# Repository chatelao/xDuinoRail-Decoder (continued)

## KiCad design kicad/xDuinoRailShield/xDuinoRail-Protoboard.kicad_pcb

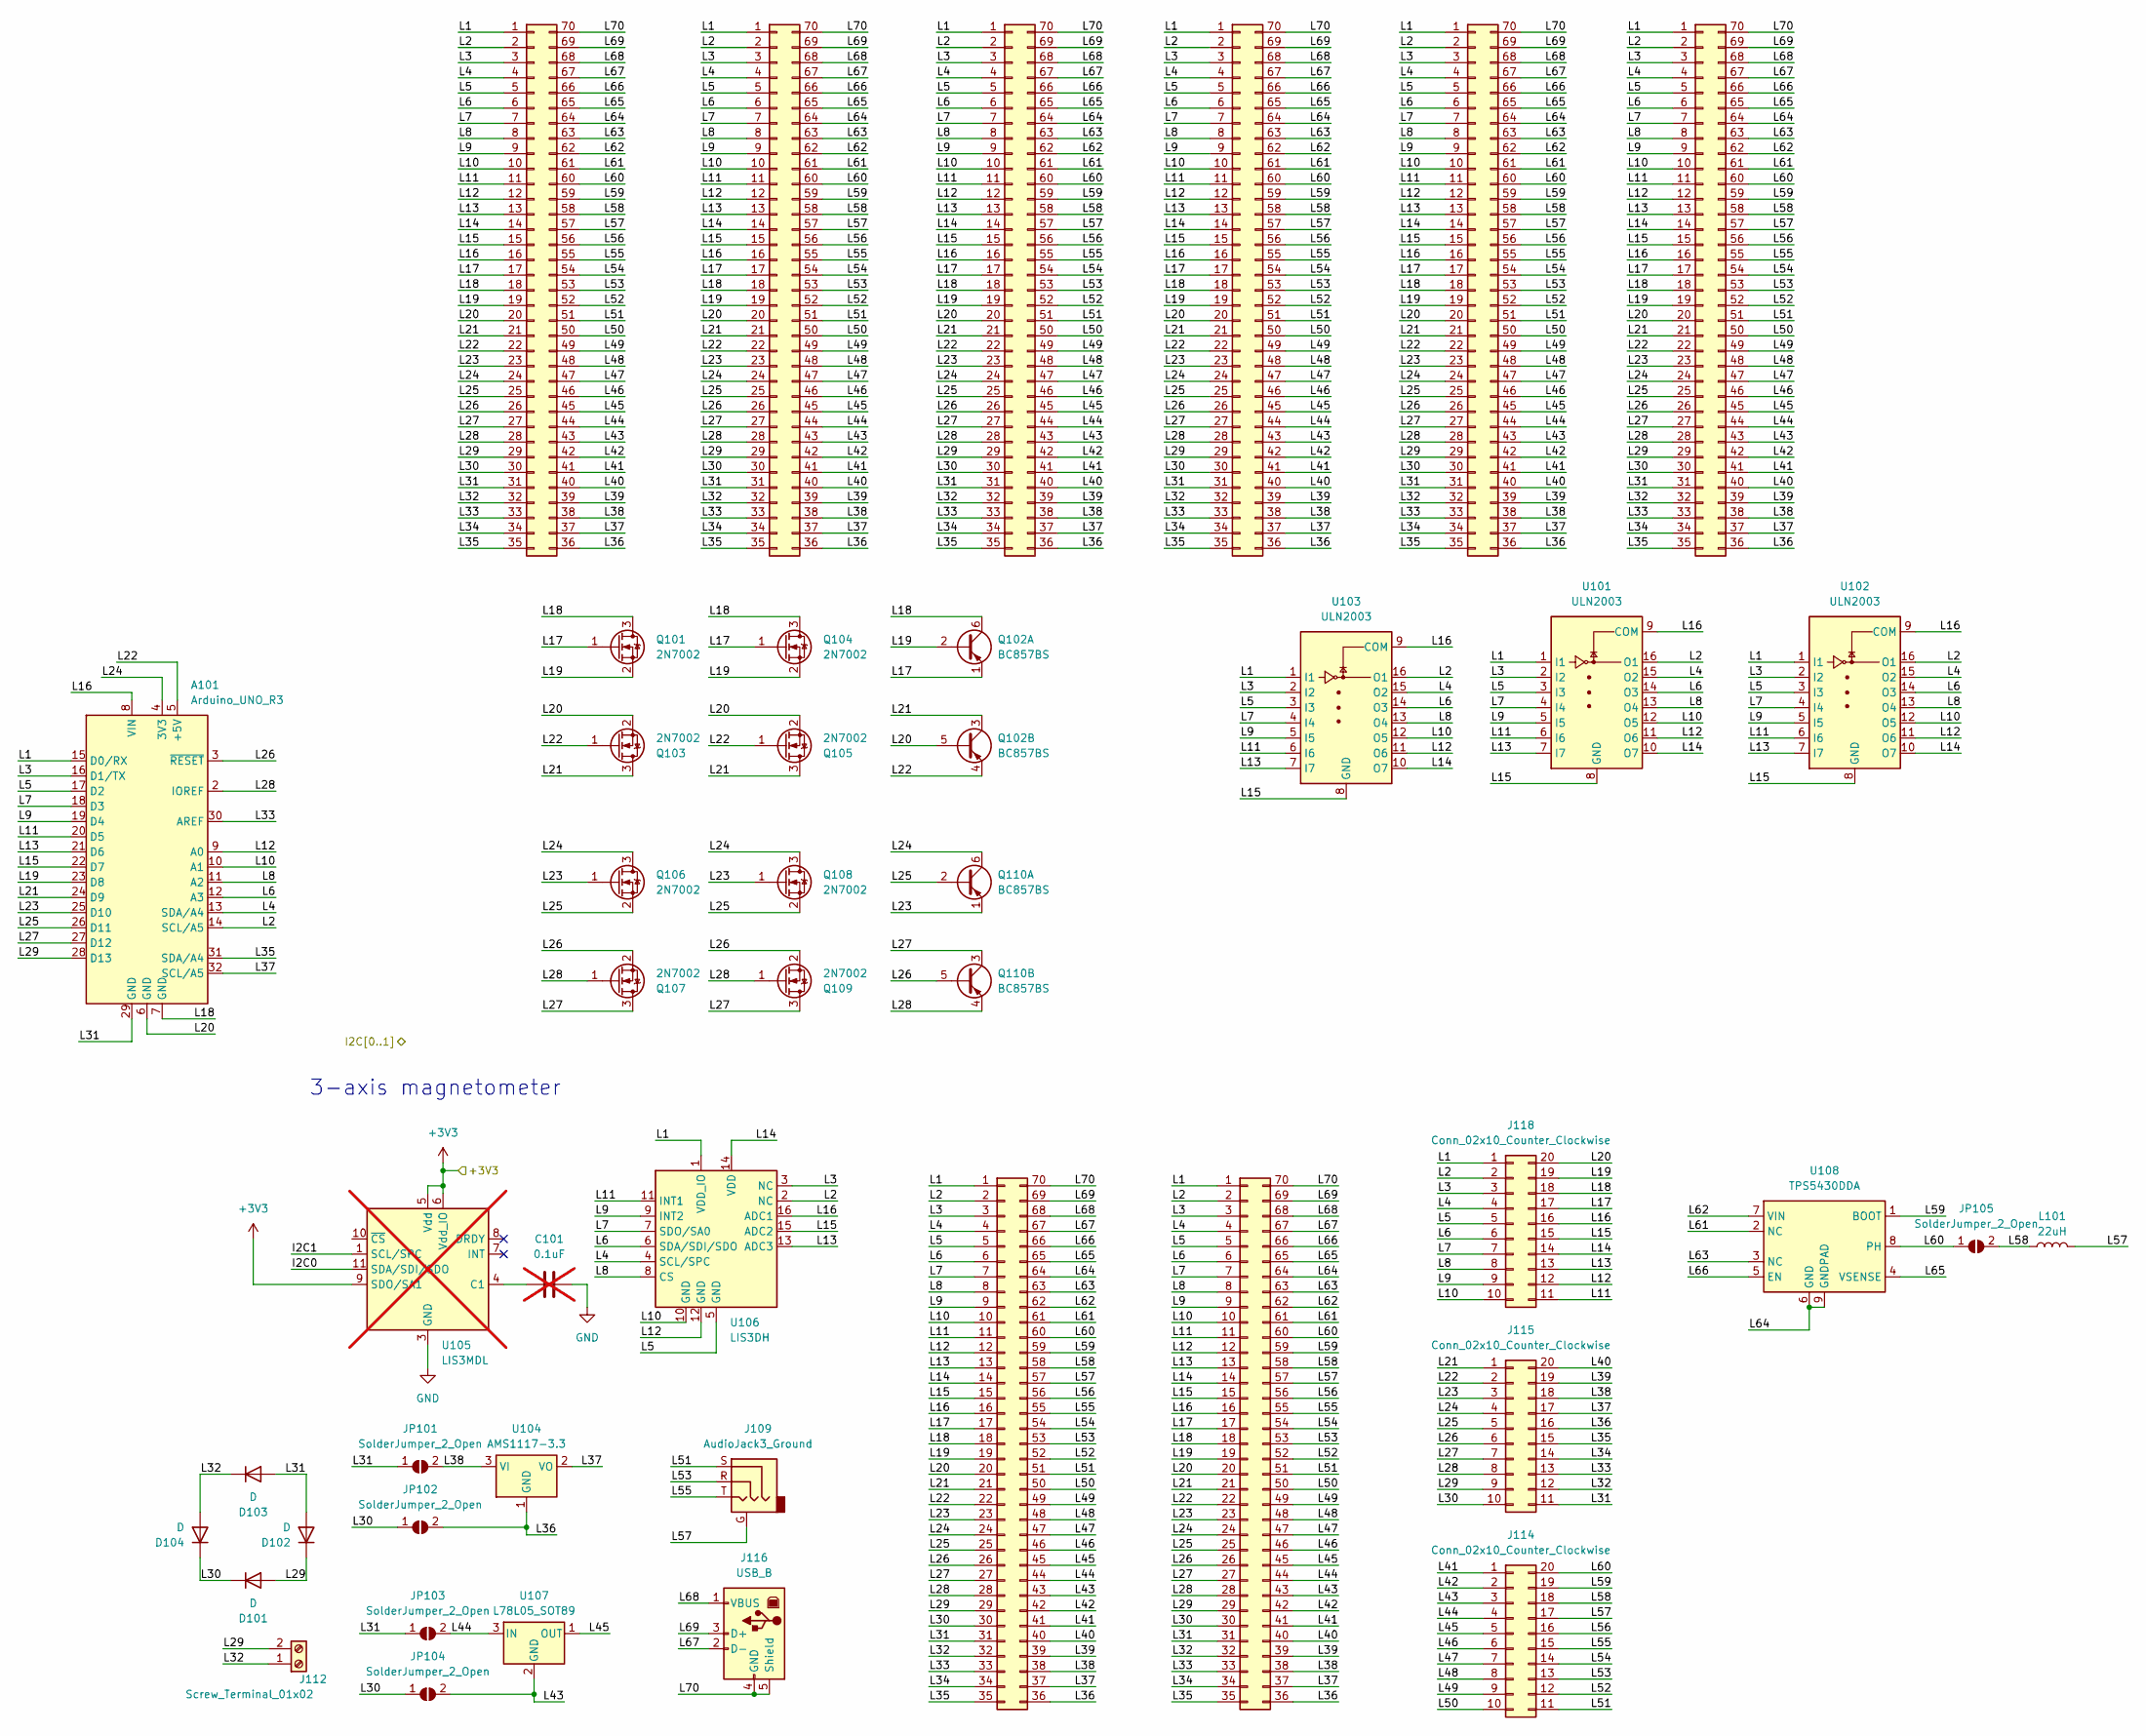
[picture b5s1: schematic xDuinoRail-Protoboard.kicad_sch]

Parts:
A101: Arduino_UNO_R3
C101: 0.1uF; C_0805_2012Metric_Pad1.18x1.45mm_HandSolder; not fitted
D101, D102, D103, D104: D; D_SMA-SMB_Universal_Handsoldering
J101, J102, J103, J104, J105, J106, J110, J111: Conn_02x35_Counter_Clockwise; PinHeader_2x35_P2.54mm_Vertical_Proto
J109: AudioJack3_Ground; Jack_3.5mm_Lumberg_1503_03_Horizontal
J112: Screw_Terminal_01x02; TerminalBlock_bornier-2_P5.08mm
J114: Conn_02x10_Counter_Clockwise; PinHeader_2x10_P1.27mm_Vertical
J115: Conn_02x10_Counter_Clockwise; PinHeader_2x10_P1.00mm_Vertical
J116: USB_B; USB_B_OST_USB-B1HSxx_Horizontal
J118: Conn_02x10_Counter_Clockwise; PinHeader_2x10_P2.00mm_Vertical
JP101, JP102, JP103, JP104, JP105: SolderJumper_2_Open; SolderJumper-2_P1.3mm_Open_TrianglePad1.0x1.5mm
L101: 22uH; L_12x12mm_H8mm; LCSC C693888
Q101, Q103, Q104, Q105, Q106, Q107, Q108, Q109: 2N7002; SOT-23_Handsoldering
Q102, Q110: BC857BS; SOT-363_SC-70-6
U101, U103: ULN2003; SOIC-16_3.9x9.9mm_P1.27mm
U102: ULN2003; SSOP-16_3.9x4.9mm_P0.635mm
U104: AMS1117-3.3; SOT-223-3_TabPin2
U105: LIS3MDL; LGA-12_2x2mm_P0.5mm; LCSC C478483; not fitted
U106: LIS3DH; LGA-16_3x3mm_P0.5mm_LayoutBorder3x5y; LCSC C15134
U107: L78L05_SOT89; SOT-89-3
U108: TPS5430DDA; TI_SO-PowerPAD-8_ThermalVias; LCSC C9864

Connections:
/L1: A101.15 (D0/RX), J101.1, J102.1, J103.1, J104.1, J105.1, J106.1, J110.1, J111.1, J118.1, U101.1 (I1), U102.1 (I1), U103.1 (I1), U106.1 (VDD_IO)
/L2: A101.14 (SCL/A5), J101.2, J102.2, J103.2, J104.2, J105.2, J106.2, J110.2, J111.2, J118.2, U101.16 (O1), U102.16 (O1), U103.16 (O1), U106.2 (NC)
/L3: A101.16 (D1/TX), J101.3, J102.3, J103.3, J104.3, J105.3, J106.3, J110.3, J111.3, J118.3, U101.2 (I2), U102.2 (I2), U103.2 (I2), U106.3 (NC)
/L4: A101.13 (SDA/A4), J101.4, J102.4, J103.4, J104.4, J105.4, J106.4, J110.4, J111.4, J118.4, U101.15 (O2), U102.15 (O2), U103.15 (O2), U106.4 (SCL/SPC)
/L5: A101.17 (D2), J101.5, J102.5, J103.5, J104.5, J105.5, J106.5, J110.5, J111.5, J118.5, U101.3 (I3), U102.3 (I3), U103.3 (I3), U106.5 (GND)
/L6: A101.12 (A3), J101.6, J102.6, J103.6, J104.6, J105.6, J106.6, J110.6, J111.6, J118.6, U101.14 (O3), U102.14 (O3), U103.14 (O3), U106.6 (SDA/SDI/SDO)
/L7: A101.18 (D3), J101.7, J102.7, J103.7, J104.7, J105.7, J106.7, J110.7, J111.7, J118.7, U101.4 (I4), U102.4 (I4), U103.4 (I4), U106.7 (SDO/SA0)
/L8: A101.11 (A2), J101.8, J102.8, J103.8, J104.8, J105.8, J106.8, J110.8, J111.8, J118.8, U101.13 (O4), U102.13 (O4), U103.13 (O4), U106.8 (CS)
/L9: A101.19 (D4), J101.9, J102.9, J103.9, J104.9, J105.9, J106.9, J110.9, J111.9, J118.9, U101.5 (I5), U102.5 (I5), U103.5 (I5), U106.9 (INT2)
/L10: A101.10 (A1), J101.10, J102.10, J103.10, J104.10, J105.10, J106.10, J110.10, J111.10, J118.10, U101.12 (O5), U102.12 (O5), U103.12 (O5), U106.10 (GND)
/L11: A101.20 (D5), J101.11, J102.11, J103.11, J104.11, J105.11, J106.11, J110.11, J111.11, J118.11, U101.6 (I6), U102.6 (I6), U103.6 (I6), U106.11 (INT1)
/L12: A101.9 (A0), J101.12, J102.12, J103.12, J104.12, J105.12, J106.12, J110.12, J111.12, J118.12, U101.11 (O6), U102.11 (O6), U103.11 (O6), U106.12 (GND)
/L13: A101.21 (D6), J101.13, J102.13, J103.13, J104.13, J105.13, J106.13, J110.13, J111.13, J118.13, U101.7 (I7), U102.7 (I7), U103.7 (I7), U106.13 (ADC3)
/L14: J101.14, J102.14, J103.14, J104.14, J105.14, J106.14, J110.14, J111.14, J118.14, U101.10 (O7), U102.10 (O7), U103.10 (O7), U106.14 (VDD)
/L15: A101.22 (D7), J101.15, J102.15, J103.15, J104.15, J105.15, J106.15, J110.15, J111.15, J118.15, U101.8 (GND), U102.8 (GND), U103.8 (GND), U106.15 (ADC2)
/L16: A101.8 (VIN), J101.16, J102.16, J103.16, J104.16, J105.16, J106.16, J110.16, J111.16, J118.16, U101.9 (COM), U102.9 (COM), U103.9 (COM), U106.16 (ADC1)
/L17: J101.17, J102.17, J103.17, J104.17, J105.17, J106.17, J110.17, J111.17, J118.17, Q101.1 (G), Q102.1 (E1), Q104.1 (G)
/L18: A101.7 (GND), J101.18, J102.18, J103.18, J104.18, J105.18, J106.18, J110.18, J111.18, J118.18, Q101.3 (D), Q102.6 (C1), Q104.3 (D)
/L19: A101.23 (D8), J101.19, J102.19, J103.19, J104.19, J105.19, J106.19, J110.19, J111.19, J118.19, Q101.2 (S), Q102.2 (B1), Q104.2 (S)
/L20: A101.6 (GND), J101.20, J102.20, J103.20, J104.20, J105.20, J106.20, J110.20, J111.20, J118.20, Q102.5 (B2), Q103.2 (S), Q105.2 (S)
/L21: A101.24 (D9), J101.21, J102.21, J103.21, J104.21, J105.21, J106.21, J110.21, J111.21, J115.1, Q102.3 (C2), Q103.3 (D), Q105.3 (D)
/L22: A101.5 (+5V), J101.22, J102.22, J103.22, J104.22, J105.22, J106.22, J110.22, J111.22, J115.2, Q102.4 (E2), Q103.1 (G), Q105.1 (G)
/L23: A101.25 (D10), J101.23, J102.23, J103.23, J104.23, J105.23, J106.23, J110.23, J111.23, J115.3, Q106.1 (G), Q108.1 (G), Q110.1 (E1)
/L24: A101.4 (3V3), J101.24, J102.24, J103.24, J104.24, J105.24, J106.24, J110.24, J111.24, J115.4, Q106.3 (D), Q108.3 (D), Q110.6 (C1)
/L25: A101.26 (D11), J101.25, J102.25, J103.25, J104.25, J105.25, J106.25, J110.25, J111.25, J115.5, Q106.2 (S), Q108.2 (S), Q110.2 (B1)
/L26: A101.3 (~RESET), J101.26, J102.26, J103.26, J104.26, J105.26, J106.26, J110.26, J111.26, J115.6, Q107.2 (S), Q109.2 (S), Q110.5 (B2)
/L27: A101.27 (D12), J101.27, J102.27, J103.27, J104.27, J105.27, J106.27, J110.27, J111.27, J115.7, Q107.3 (D), Q109.3 (D), Q110.3 (C2)
/L28: A101.2 (IOREF), J101.28, J102.28, J103.28, J104.28, J105.28, J106.28, J110.28, J111.28, J115.8, Q107.1 (G), Q109.1 (G), Q110.4 (E2)
/L29: A101.28 (D13), D101.2 (A), D102.1 (K), J101.29, J102.29, J103.29, J104.29, J105.29, J106.29, J110.29, J111.29, J112.2, J115.9
/L30: D101.1 (K), D104.1 (K), J101.30, J102.30, J103.30, J104.30, J105.30, J106.30, J110.30, J111.30, J115.10, JP102.1 (A), JP104.1 (A)
/L31: A101.29 (GND), D102.2 (A), D103.2 (A), J101.31, J102.31, J103.31, J104.31, J105.31, J106.31, J110.31, J111.31, J115.11, JP101.1 (A), JP103.1 (A)
/L32: D103.1 (K), D104.2 (A), J101.32, J102.32, J103.32, J104.32, J105.32, J106.32, J110.32, J111.32, J112.1, J115.12
/L33: A101.30 (AREF), J101.33, J102.33, J103.33, J104.33, J105.33, J106.33, J110.33, J111.33, J115.13
/L34: J101.34, J102.34, J103.34, J104.34, J105.34, J106.34, J110.34, J111.34, J115.14
/L35: A101.31 (SDA/A4), J101.35, J102.35, J103.35, J104.35, J105.35, J106.35, J110.35, J111.35, J115.15
/L36: J101.36, J102.36, J103.36, J104.36, J105.36, J106.36, J110.36, J111.36, J115.16, JP102.2 (B), U104.1 (GND)
/L37: A101.32 (SCL/A5), J101.37, J102.37, J103.37, J104.37, J105.37, J106.37, J110.37, J111.37, J115.17, U104.2 (VO)
/L38: J101.38, J102.38, J103.38, J104.38, J105.38, J106.38, J110.38, J111.38, J115.18, JP101.2 (B), U104.3 (VI)
/L39: J101.39, J102.39, J103.39, J104.39, J105.39, J106.39, J110.39, J111.39, J115.19
/L40: J101.40, J102.40, J103.40, J104.40, J105.40, J106.40, J110.40, J111.40, J115.20
/L41: J101.41, J102.41, J103.41, J104.41, J105.41, J106.41, J110.41, J111.41, J114.1
/L42: J101.42, J102.42, J103.42, J104.42, J105.42, J106.42, J110.42, J111.42, J114.2
/L43: J101.43, J102.43, J103.43, J104.43, J105.43, J106.43, J110.43, J111.43, J114.3, JP104.2 (B), U107.2 (GND)
/L44: J101.44, J102.44, J103.44, J104.44, J105.44, J106.44, J110.44, J111.44, J114.4, JP103.2 (B), U107.3 (IN)
/L45: J101.45, J102.45, J103.45, J104.45, J105.45, J106.45, J110.45, J111.45, J114.5, U107.1 (OUT)
/L46: J101.46, J102.46, J103.46, J104.46, J105.46, J106.46, J110.46, J111.46, J114.6
/L47: J101.47, J102.47, J103.47, J104.47, J105.47, J106.47, J110.47, J111.47, J114.7
/L48: J101.48, J102.48, J103.48, J104.48, J105.48, J106.48, J110.48, J111.48, J114.8
/L49: J101.49, J102.49, J103.49, J104.49, J105.49, J106.49, J110.49, J111.49, J114.9
/L50: J101.50, J102.50, J103.50, J104.50, J105.50, J106.50, J110.50, J111.50, J114.10
/L51: J101.51, J102.51, J103.51, J104.51, J105.51, J106.51, J109.S, J110.51, J111.51, J114.11
/L52: J101.52, J102.52, J103.52, J104.52, J105.52, J106.52, J110.52, J111.52, J114.12
/L53: J101.53, J102.53, J103.53, J104.53, J105.53, J106.53, J109.R, J110.53, J111.53, J114.13
/L54: J101.54, J102.54, J103.54, J104.54, J105.54, J106.54, J110.54, J111.54, J114.14
/L55: J101.55, J102.55, J103.55, J104.55, J105.55, J106.55, J109.T, J110.55, J111.55, J114.15
/L56: J101.56, J102.56, J103.56, J104.56, J105.56, J106.56, J110.56, J111.56, J114.16
/L57: J101.57, J102.57, J103.57, J104.57, J105.57, J106.57, J109.G, J110.57, J111.57, J114.17, L101.2
/L58: J101.58, J102.58, J103.58, J104.58, J105.58, J106.58, J110.58, J111.58, J114.18, JP105.2 (B), L101.1
/L59: J101.59, J102.59, J103.59, J104.59, J105.59, J106.59, J110.59, J111.59, J114.19, U108.1 (BOOT)
/L60: J101.60, J102.60, J103.60, J104.60, J105.60, J106.60, J110.60, J111.60, J114.20, JP105.1 (A), U108.8 (PH)
/L61: J101.61, J102.61, J103.61, J104.61, J105.61, J106.61, J110.61, J111.61, U108.2 (NC)
/L62: J101.62, J102.62, J103.62, J104.62, J105.62, J106.62, J110.62, J111.62, U108.7 (VIN)
/L63: J101.63, J102.63, J103.63, J104.63, J105.63, J106.63, J110.63, J111.63, U108.3 (NC)
/L64: J101.64, J102.64, J103.64, J104.64, J105.64, J106.64, J110.64, J111.64, U108.6 (GND), U108.9 (GNDPAD)
/L65: J101.65, J102.65, J103.65, J104.65, J105.65, J106.65, J110.65, J111.65, U108.4 (VSENSE)
/L66: J101.66, J102.66, J103.66, J104.66, J105.66, J106.66, J110.66, J111.66, U108.5 (EN)
/L67: J101.67, J102.67, J103.67, J104.67, J105.67, J106.67, J110.67, J111.67, J116.2 (D-)
/L68: J101.68, J102.68, J103.68, J104.68, J105.68, J106.68, J110.68, J111.68, J116.1 (VBUS)
/L69: J101.69, J102.69, J103.69, J104.69, J105.69, J106.69, J110.69, J111.69, J116.3 (D+)
/L70: J101.70, J102.70, J103.70, J104.70, J105.70, J106.70, J110.70, J111.70, J116.4 (GND), J116.5 (Shield)
unnamed: C101.1, U105.4 (C1)
unnamed: C101.2, U105.2 (GND), U105.3 (GND), U105.12 (GND)
unnamed: U105.5 (Vdd), U105.6 (Vdd_IO), U105.9 (SDO/SA1)

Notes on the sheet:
3-axis magnetometer

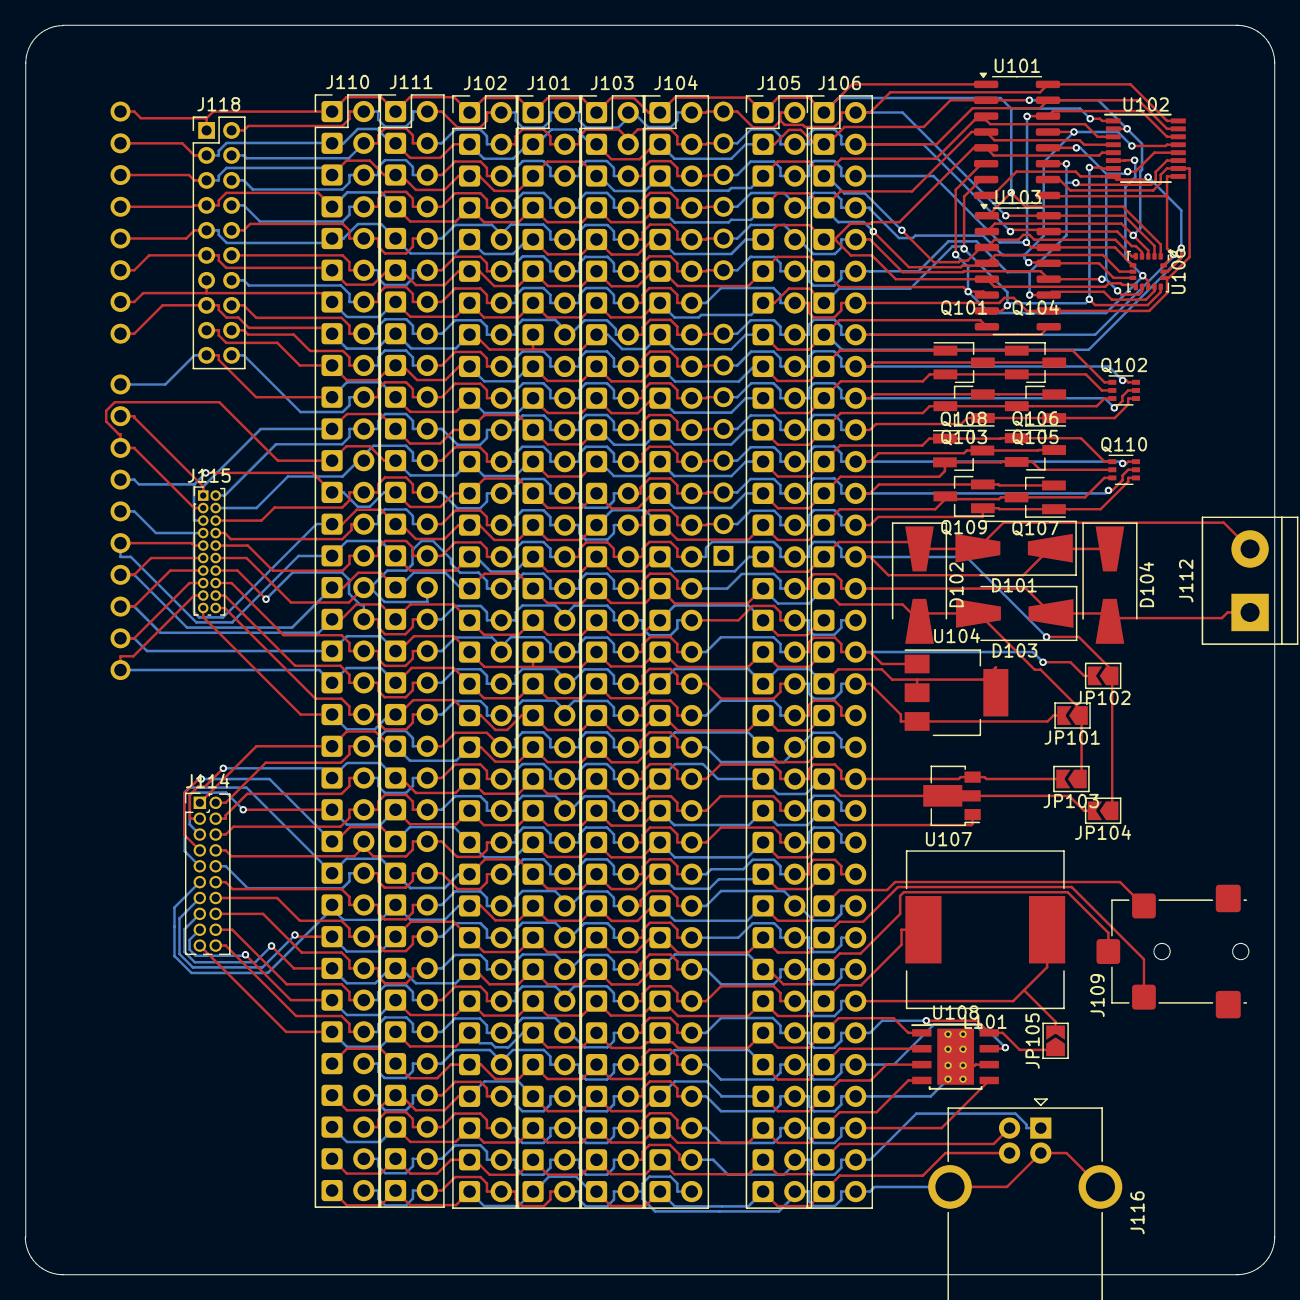
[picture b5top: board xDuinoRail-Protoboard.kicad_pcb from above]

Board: 2 copper layers, 100.0 x 100.0 mm, 42 parts (1 on the bottom side), 70 nets.

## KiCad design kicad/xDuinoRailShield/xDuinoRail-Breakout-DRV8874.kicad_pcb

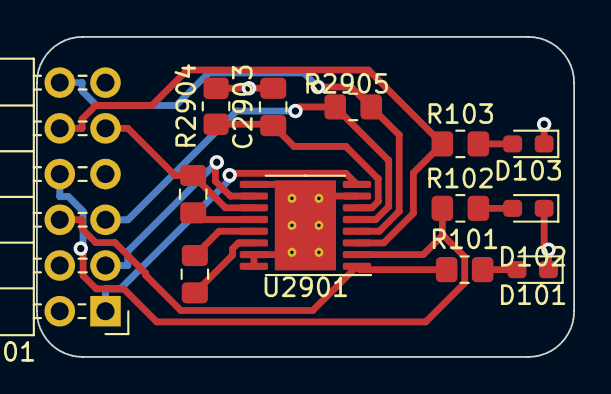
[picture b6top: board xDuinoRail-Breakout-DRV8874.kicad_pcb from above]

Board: 2 copper layers, 29.8 x 17.8 mm, 13 parts (0 on the bottom side), 16 nets.

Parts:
C2901: 100nF; C_0805_2012Metric_Pad1.18x1.45mm_HandSolder
C2902, C2903: 22nF; C_0805_2012Metric_Pad1.18x1.45mm_HandSolder
D101: LED_RED; LED_0603_1608Metric_Pad1.05x0.95mm_HandSolder
D102: LED_YELLOW; LED_0603_1608Metric_Pad1.05x0.95mm_HandSolder
D103: LED_GREEN; LED_0603_1608Metric_Pad1.05x0.95mm_HandSolder
J101: Conn_02x06_Odd_Even; PinHeader_2x06_P2.54mm_Horizontal
R101, R102, R103: 470R; R_0805_2012Metric_Pad1.20x1.40mm_HandSolder
R2904: 1k5; R_0805_2012Metric_Pad1.20x1.40mm_HandSolder
R2905: 47k; R_0805_2012Metric_Pad1.20x1.40mm_HandSolder
U2901: DRV8874PWPR; HTSSOP-16-1EP_4.4x5mm_P0.65mm_EP3.4x5mm_Mask2.46x2.31mm_The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

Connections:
+3V3: J101.5, R2905.1, U2901.5 (VRef)
+VIN: C2901.2, J101.9, U2901.11 (VM)
/BRAKE: J101.6, R101.1, U2901.1 (EN/IN1)
/DCC0: J101.1, U2901.8 (OUT1)
/DCC1: J101.3, U2901.10 (OUT2)
/DIR: J101.8, R102.1, U2901.2 (PH/IN2)
/PWM: J101.10, R103.1, U2901.3 (nSleep)
/centrale-driver-8874/CPH: C2902.1, U2901.13 (CPH)
/centrale-driver-8874/CPL: C2902.2, U2901.14 (CPL)
/centrale-driver-8874/SENSE: J101.12, R2905.2, U2901.4 (nFAULT)
/centrale-driver-8874/VCP: C2901.1, U2901.12 (VCP)
/centrale-driver-8874/iPROP: C2903.1, R2904.1, U2901.6 (IPROPI)
GND: C2903.2, D101.1 (K), D102.1 (K), D103.1 (K), J101.7, R2904.2, U2901.7 (IMODE), U2901.9 (GND), U2901.15 (GND), U2901.16 (PMODE), U2901.17 (GND)
unnamed: D101.2 (A), R101.2
unnamed: D102.2 (A), R102.2
unnamed: D103.2 (A), R103.2

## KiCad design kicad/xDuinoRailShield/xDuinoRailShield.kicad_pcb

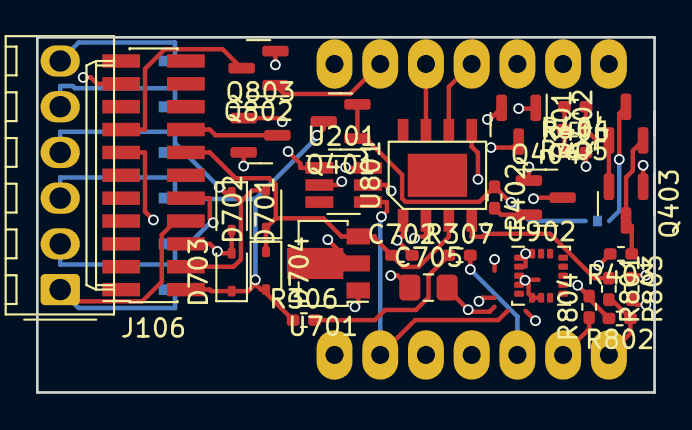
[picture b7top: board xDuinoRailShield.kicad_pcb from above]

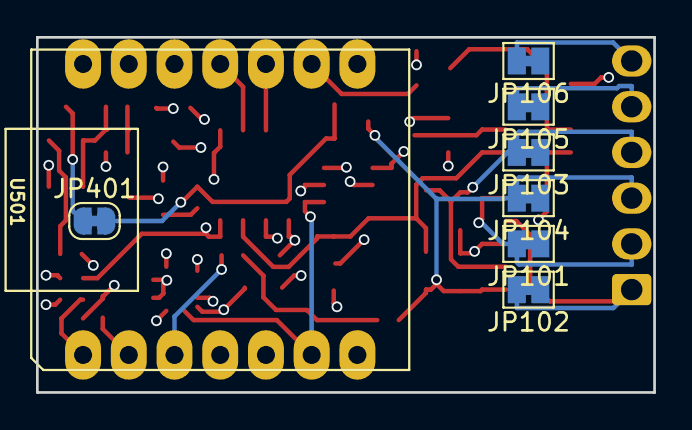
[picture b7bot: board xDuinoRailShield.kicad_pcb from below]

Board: 4 copper layers, 34.3 x 19.7 mm, 38 parts (8 on the bottom side), 31 nets.

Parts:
C702: 1uF; C_0402_1005Metric_Pad0.74x0.62mm_HandSolder
C705: 47uF; C_0805_2012Metric_Pad1.18x1.45mm_HandSolder
D701, D702, D703, D704: 1N5819WS; D_SOD-323
J104: Conn_01x06; Molex_KK-254_AE-6410-06A_1x06_P2.54mm_Vertical
J106: 21mtc_mrkl; PinSocket_2x11_P1.27mm_Vertical_SMD
JP101, JP102, JP103, JP104, JP105, JP106: SolderJumper_2_Bridged; SolderJumper-2_P1.3mm_Bridged_Pad1.0x1.5mm
JP401: J_EnableRailcom; SolderJumper-2_P1.3mm_Bridged_RoundedPad1.0x1.5mm
Q401, Q404: S8050; SOT-23
Q402, Q403: S8550; SOT-23
Q801, Q802, Q803: 2N7002; SOT-23
R306, R307, R402, R403, R801, R803: 10k; R_0402_1005Metric_Pad0.72x0.64mm_HandSolder
R404, R405, R406: 10R; R_0402_1005Metric_Pad0.72x0.64mm_HandSolder
R802, R804: 1K; R_0402_1005Metric_Pad0.72x0.64mm_HandSolder
U201: MCP4725xxx-xCH; SOT-23-6_Handsoldering
U501: MOUDLE-SEEEDUINO-XIAO-ESP32C3; MOUDLE14P-SMD-2.54-21X17.8MM
U701: HT7533-1; SOT-89-3
U801: BDR6133
U902: LIS3DH; LGA-16_3x3mm_P0.5mm_LayoutBorder3x5y

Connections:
+3V3: C705.1, Q403.1 (E), R406.2, U201.3 (VDD), U201.6 (A0), U501.12 (3V3), U701.1 (OUT), U801.2 (VCC), U902.1 (VDD_IO), U902.8 (CS), U902.14 (VDD)
/AUX1: Q803.1 (G), U501.5 (A4)
/Audio Interfaces/I2C0: U201.5 (SCL), U501.7 (SCL_A6), U902.4 (SCL/SPC)
/Audio Interfaces/I2C1: U201.4 (SDA), U501.6 (SDA_A5), U902.6 (SDA/SDI/SDO)
/Audio Interfaces/SPEAKER1: J106.19, U201.1 (VOUT)
/Connectors 21mtc / PluXX / NEMA/AMP_AUX1: J106.16, Q803.3 (D)
/Connectors 21mtc / PluXX / NEMA/AMP_FUNC0: J106.13, Q801.3 (D)
/Connectors 21mtc / PluXX / NEMA/AMP_FUNC1: J106.15, Q802.3 (D)
/Connectors 21mtc / PluXX / NEMA/AMP_MOTOR0: J104.2, J106.10, JP101.2 (B), R801.1, U801.4 (OUTA)
/Connectors 21mtc / PluXX / NEMA/AMP_MOTOR1: J104.1, J106.8, JP102.2 (B), R803.1, U801.5 (OUTB)
/Connectors 21mtc / PluXX / NEMA/FUNC0: J104.6, JP106.2 (B)
/Connectors 21mtc / PluXX / NEMA/FUNC1: J104.5, JP105.2 (B)
/DCC0: D701.1 (K), D702.2 (A), J104.4, J106.4, JP103.2 (B), Q404.3 (C)
/DCC1: D703.1 (K), D704.2 (A), J104.3, J106.2, JP104.2 (B), Q401.3 (C), R306.1
/MCU Carrier Board/EMF_MOTOR0: R801.2, R802.1, U501.1 (A0)
/MCU Carrier Board/EMF_MOTOR1: R803.2, R804.1, U501.2 (A1)
/MCU Carrier Board/FUNC0: Q801.1 (G), U501.8 (A7_RX)
/MCU Carrier Board/FUNC1: Q802.1 (G), U501.9 (A8_SCK)
/MCU Carrier Board/MOTOR0: U501.11 (A10_MOSI), U801.6 (INA)
/MCU Carrier Board/MOTOR1: U501.10 (A9_MISO), U801.7 (INB)
/Railcom-Feedback/RC_CURR: Q402.1 (E), Q403.2 (B), R404.1, R405.1
/Railcom-Feedback/RC_FB_IN: Q402.2 (B), Q403.3 (C), R403.1
/Railcom-Feedback/RC_ON_OFF: Q404.2 (B), R402.2
/Railcom-Feedback/RC_SIGNAL: JP401.2 (B), Q401.1 (E), Q401.2 (B), R402.1
DCC_MM: R307.2, U501.3 (A2)
GND: C702.2, C705.2, D701.2 (A), D703.2 (A), J106.6, Q404.1 (E), Q801.2 (S), Q802.2 (S), Q803.2 (S), R802.2, R804.2, U201.2 (VSS), U501.13 (GND), U701.2 (GND), U801.1 (GND), U902.5 (GND), U902.10 (GND), U902.12 (GND)
unnamed: JP401.1 (A), Q402.3 (C)
unnamed: R306.2, R307.1
unnamed: R404.2, R405.2, R406.1
RAILCOM_DATA: R403.2, U501.4 (A3)
U+: C702.1, D702.1 (K), D704.1 (K), J106.14, U701.3 (IN), U801.3 (VM)
